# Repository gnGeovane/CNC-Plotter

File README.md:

# CNC-Plotter

Aqui você encontrará os arquivos necessários para fazer uma CNC Plotter e controlá-la.

# Código:

Todos os códigos e a biblioteca para motores de passo foram feitos do zero, linha-a-linha, especificamente para este projeto.
  
As versões mais recentes do código para o arduino incluem suporte para:

- Drivers de motores de passo L293D, ULN2803 e ULN2003;
- Sensores de fim de curso;
- Botão stop;
- Controle de motores de passo com ShiftRegister 74595 usando FullSteps e HalfSteps;
- Motores de passo bipolares ou unipolares.

# G-CODE Sender

Para a comunicação do computador com o arduino para o envio do G-CODE do desenho, foi feito um G-CODE Sender do zero, programado no processing 4.
Este arquivo, quando executado no compilador processing, cria uma interface gráfica simples mostrando os comandos de controle da CNC, como:

- Movimentar algum eixo;
- Subir e descer a caneta;
- Ir para a posição Home;
- Buscar um arquivo G-CODE no Windows Explorer e iniciar o envio serial.

# APP para android

Também foi criado um app em Kotlin no Android Studio que funciona de forma similar ao programa G-CODE Sender do item anterior. Porém, o diferencial do app para celular é a possibilidade de controlar a máquina à distância via Bluetooth.

<br> Demonstração do app aqui: https://youtu.be/cIXA6mVwmhk

# Criação de G-CODE

Para criar o arquivo de coordenadas (G-CODE) de uma imagem para desenhá-la, é necessário utilizar o software InksCape (gratuito) ou Autodesk ArtCAM (Pago). Caso queira plotar um circuito em uma PCB, poderá converter arquivos Gerber(.gbr) e Excellon(.drl) em G-CODE utilizando o software de código aberto FlatCAM.
  
# Veja os resultados atuais do projeto:

<br> 

# Assista a CNC em ação no YouTube!

[Desenhando ícone do app (controle por Bluetooth com app)](https://youtu.be/TSL-Wnw5sp4)

<br> [Desenhando um avião (controle via porta serial)](https://www.youtube.com/watch?v=H5-JilG_zv4)

<br> [short - Desenhando um touro (Controle via porta serial)](https://www.youtube.com/shorts/jxCdN6tVYik)

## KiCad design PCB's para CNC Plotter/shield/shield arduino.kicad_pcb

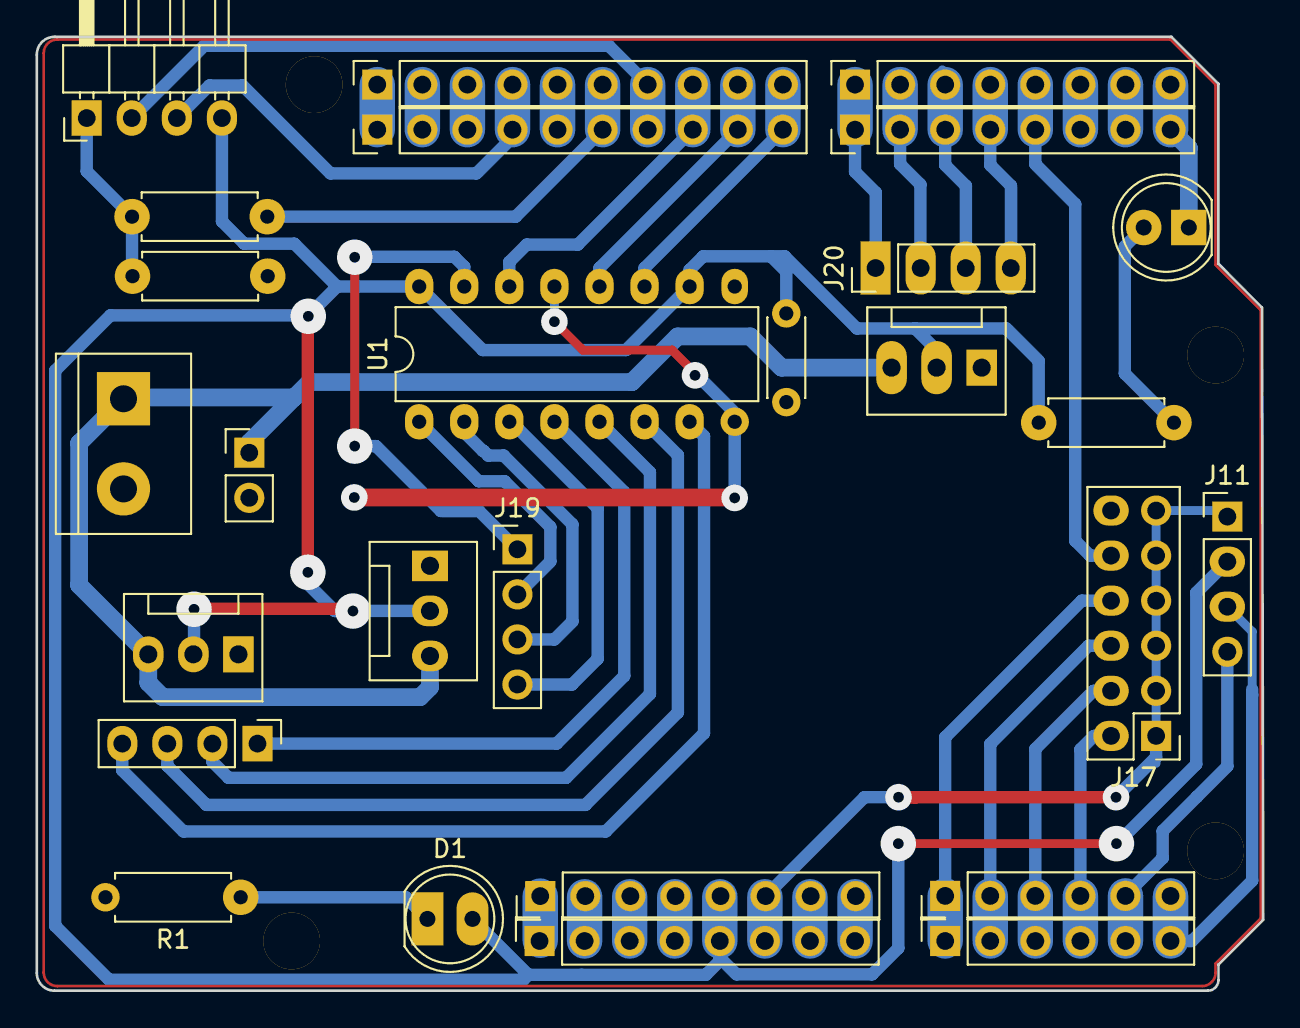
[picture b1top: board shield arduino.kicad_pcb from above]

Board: 2 copper layers, 69.1 x 53.8 mm, 31 parts (0 on the bottom side), 38 nets.

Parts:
C4: 0.1uF; C_Disc_D4.3mm_W1.9mm_P5.00mm
D1, D2: LED; LED_D5.0mm
J1: Power; PinSocket_1x08_P2.54mm_Vertical
J2: Digital/PWM; PinSocket_1x10_P2.54mm_Vertical
J3: Analog; PinSocket_1x06_P2.54mm_Vertical
J4: Digital/PWM; PinSocket_1x08_P2.54mm_Vertical
J5: Vdrive; TerminalBlock_bornier-2_P5.08mm
J8: FAN; PinHeader_1x02_P2.54mm_Vertical
J10: Bluetooth; PinHeader_1x04_P2.54mm_Horizontal
J11: I2C; PinHeader_1x04_P2.54mm_Vertical
J12: MYF; PinHeader_1x04_P2.54mm_Vertical
J13: Power; PinHeader_1x08_P2.54mm_Vertical
J14: Analog; PinHeader_1x06_P2.54mm_Vertical
J15: Digital/PWM; PinHeader_1x10_P2.54mm_Vertical
J16: Digital/PWM; PinHeader_1x08_P2.54mm_Vertical
J17: Sensores; PinHeader_2x06_P2.54mm_Vertical
J18, J18#2, J18#3: Drivers VCC; FanPinHeader_1x03_P2.54mm_Vertical
J19: MXF; PinHeader_1x04_P2.54mm_Vertical
J20: MZF; PinHeader_1x04_P2.54mm_Vertical
MH1, MH2, MH3, MH4: MountingHole_3.2mm
R1: 4,7k; R_Axial_DIN0207_L6.3mm_D2.5mm_P7.62mm_Horizontal
R2, R4: 1k; R_Axial_DIN0207_L6.3mm_D2.5mm_P7.62mm_Horizontal
R3: 1.8k; R_Axial_DIN0207_L6.3mm_D2.5mm_P7.62mm_Horizontal
U1: 74HC595; DIP-16_W7.62mm

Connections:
+5V: C4.2, D1.2 (A), J1.5, J10.4, J11.2, J13.5, J17.12, J18.2, J18#2.2, J18#3.2, R4.1, U1.10 (~SRCLR), U1.16 (VCC)
/2: J4.6, J16.6
/4: J4.4, J16.4, J20.4
/7: J4.1, J16.1, J20.1
/8: J2.10, J15.10, U1.11 (SRCLK)
/12: J2.6, J15.6, R2.1
/13: J2.5, J15.5
/*3: J4.5, J16.5, J17.10
/*5: J4.3, J16.3, J20.3
/*6: J4.2, J16.2, J20.2
/*9: J2.9, J15.9, U1.12 (RCLK)
/*10: J2.8, J15.8, U1.14 (SER)
/*11: J2.7, J10.2, J15.7
/A0: J3.1, J14.1, J17.8
/A1: J3.2, J14.2, J17.6
/A2: J3.3, J14.3, J17.4
/A3: J3.4, J14.4, J17.2
/AREF: J2.3, J15.3
/IOREF: J1.2, J13.2
/RX/0: D2.1 (K), J4.8, J16.8
/SCL/A5: J2.1, J3.6, J11.3, J14.6, J15.1
/SDA/A4: J2.2, J3.5, J11.4, J14.5, J15.2
/TX/1: J4.7, J16.7
/Vin: J1.8, J13.8
/~RESET: J1.3, J13.3
Earth: C4.1, J1.6, J1.7, J2.4, J5.2, J8.2, J10.3, J11.1, J13.6, J13.7, J15.4, J17.1, J17.3, J17.5, J17.7, J17.9, J17.11, J18.1, J18#2.1, J18#3.1, R1.2, R3.1, U1.8 (GND), U1.13 (~OE)
unnamed: D1.1 (K), R1.1
unnamed: D2.2 (A), R4.2
unnamed: J10.1, R2.2, R3.2
unnamed: J12.1, U1.4 (QE)
unnamed: J12.2, U1.5 (QF)
unnamed: J12.3, U1.6 (QG)
unnamed: J12.4, U1.7 (QH)
unnamed: J19.1, U1.15 (QA)
unnamed: J19.2, U1.1 (QB)
unnamed: J19.3, U1.2 (QC)
unnamed: J19.4, U1.3 (QD)
Vdrive: J5.1, J8.1, J18.3, J18#2.3, J18#3.3

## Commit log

2025-06-23 Envio dos arquivos do projeto
2025-06-24 Modificação no README e na pinagem do arduino
2025-06-24 Organização de arquivos e versionamento de códigos.
2025-07-17 Removido arquivos Gerbers antigos
2025-08-30 v1.2.5 — Lançamento: correções e melhorias
2025-10-11 Atualização de firmware e adição do APP CNC Plotter Sender
2025-10-12 Update do ReadMe.md e modificações de código
